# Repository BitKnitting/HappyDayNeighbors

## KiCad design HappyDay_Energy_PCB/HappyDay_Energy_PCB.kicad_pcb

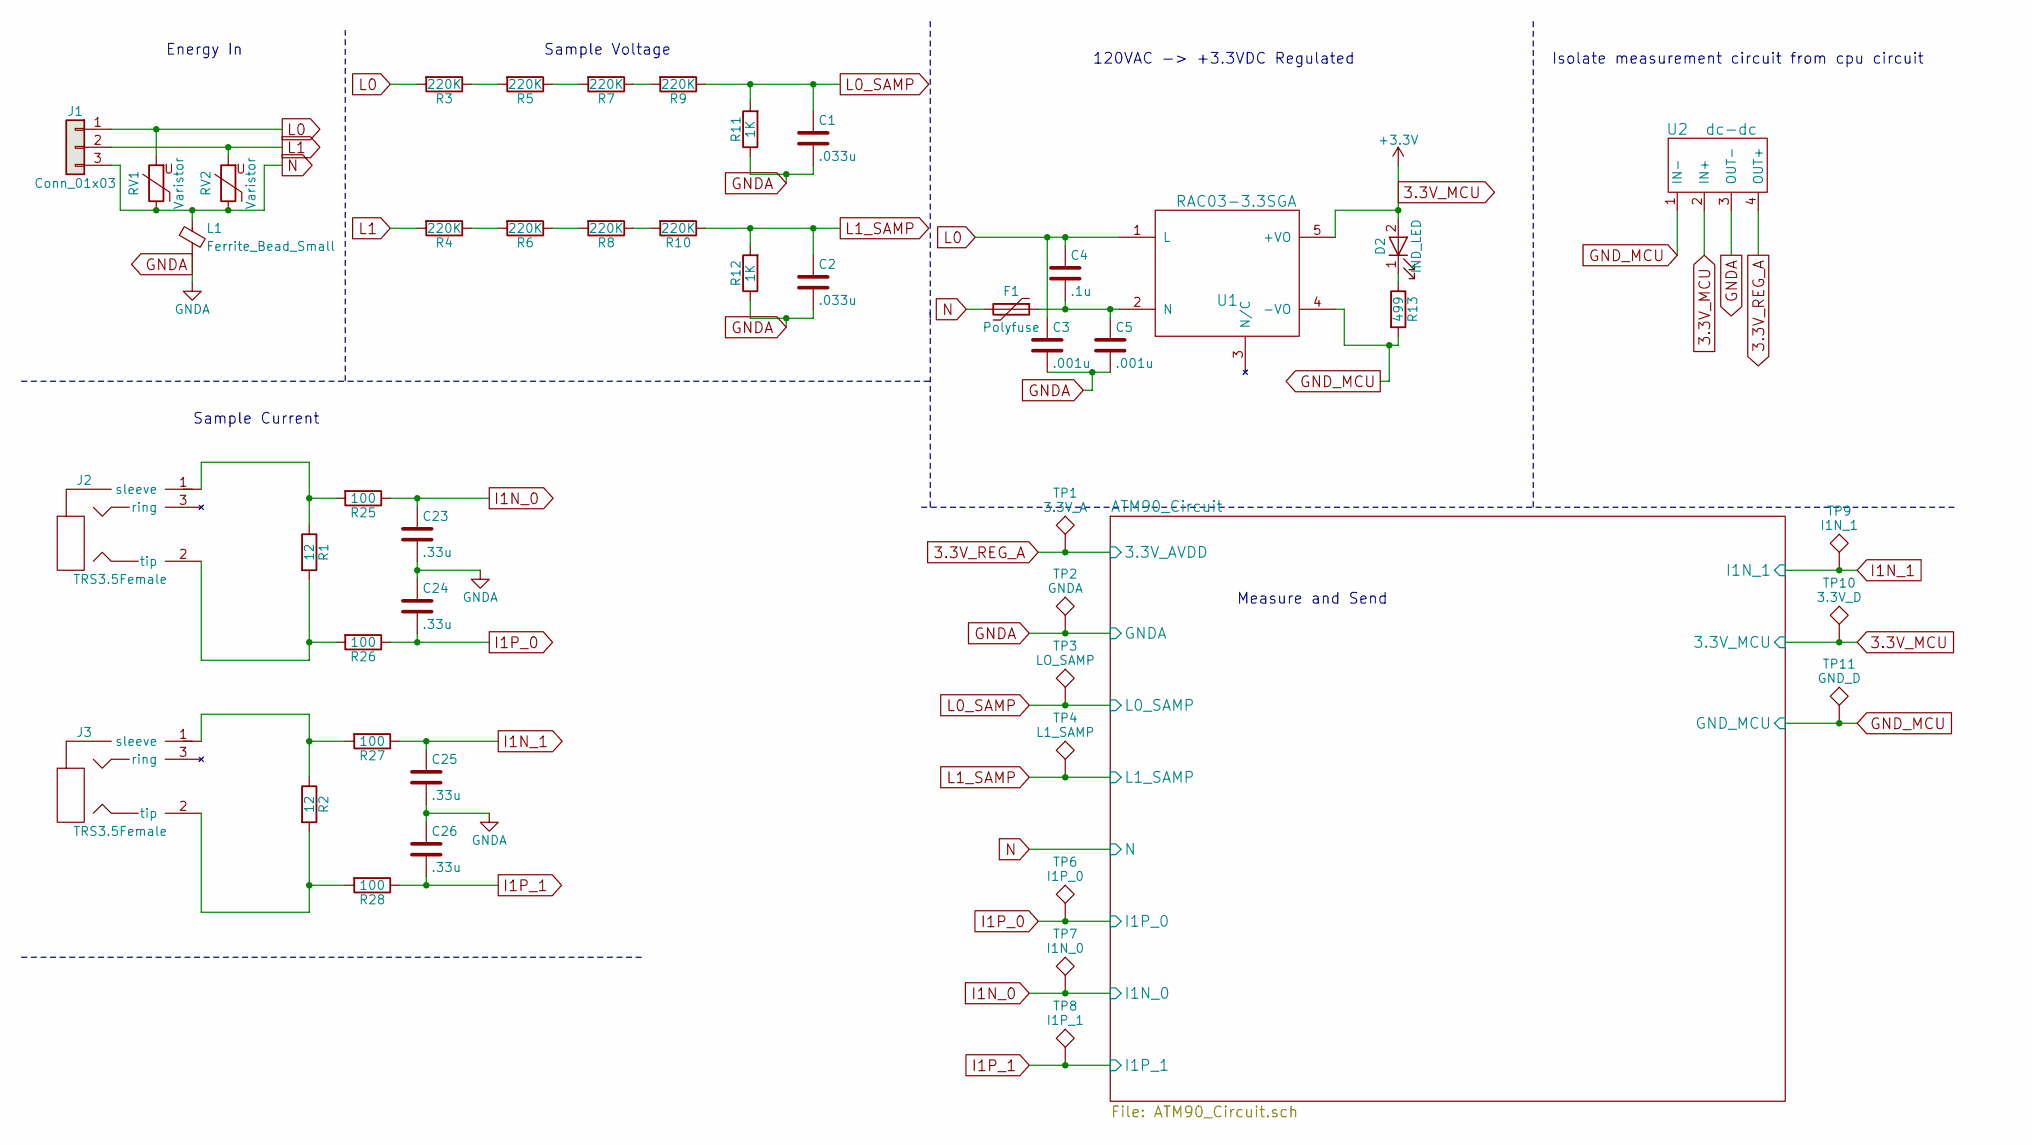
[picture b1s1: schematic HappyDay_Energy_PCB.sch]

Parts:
C1, C2: .033u; C_0805
C3, C5: .001u; C_0805
C4: .1u; C_0805
C23, C24, C25, C26: .33u; C_0805
D2: IND_LED; C_1206_HandSoldering
F1: Polyfuse; POLYFUSE
J1: Conn_01x03; 3PinConnector
J2, J3: TRS3.5Female; Audio-Jack
L1: Ferrite_Bead_Small; C_1206
R1, R2: 12; C_0805
R3, R4, R5, R6, R7, R8, R9, R10: 220K; C_1206
R11, R12: 1K; C_0805
R13: 499; C_0805
R25, R26, R27, R28: 100; C_0805
RV1, RV2: Varistor; MOV
TP1: 3.3V_A; Test_Point_Pad_d2.0mm
TP2: GNDA; Test_Point_Pad_d2.0mm
TP3: LO_SAMP; Test_Point_Pad_d2.0mm
TP4: L1_SAMP; Test_Point_Pad_d2.0mm
TP6: I1P_0; Test_Point_Pad_d2.0mm
TP7: I1N_0; Test_Point_Pad_d2.0mm
TP8: I1P_1; Test_Point_Pad_d2.0mm
TP9: I1N_1; Test_Point_Pad_d2.0mm
TP10: 3.3V_D; Test_Point_Pad_d2.0mm
TP11: GND_D; Test_Point_Pad_d2.0mm
U1: RAC03-3.3SGA; RAC03-GA
U2: dc-dc; DC-DC

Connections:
3.3V_MCU: D2.2 (A), TP10.1, U1.5 (+VO), U2.2 (IN+); also elsewhere on the board
3.3V_REG_A: TP1.1, U2.4 (OUT+); also elsewhere on the board
GNDA: C1.2, C2.2, C3.2, C5.2, C23.2, C24.1, C25.2, C26.1, L1.2, R11.1, R12.1, TP2.1, U2.3 (OUT-); also elsewhere on the board
GND_MCU: R13.2, TP11.1, U1.4 (-VO), U2.1 (IN-); also elsewhere on the board
I1N_0: C23.1, R25.1, TP7.1; also elsewhere on the board
I1N_1: C25.1, R27.1, TP9.1; also elsewhere on the board
I1P_0: C24.2, R26.1, TP6.1; also elsewhere on the board
I1P_1: C26.2, R28.1, TP8.1; also elsewhere on the board
L0: C3.1, C4.1, J1.1, R3.2, RV1.2, U1.1 (L)
L0_SAMP: C1.1, R9.1, R11.2, TP3.1; also elsewhere on the board
L1: J1.2, R4.2, RV2.2
L1_SAMP: C2.1, R10.1, R12.2, TP4.1; also elsewhere on the board
N: F1.2, J1.3, L1.1, RV1.1, RV2.1; also elsewhere on the board
unnamed: C4.2, C5.1, F1.1, U1.2 (N)
unnamed: D2.1 (K), R13.1
unnamed: J2.1 (sleeve), R1.1, R25.2
unnamed: J2.2 (tip), R1.2, R26.2
unnamed: J3.1 (sleeve), R2.1, R27.2
unnamed: J3.2 (tip), R2.2, R28.2
unnamed: R3.1, R5.2
unnamed: R4.1, R6.2
unnamed: R5.1, R7.2
unnamed: R6.1, R8.2
unnamed: R7.1, R9.2
unnamed: R8.1, R10.2

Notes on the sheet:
Energy In
Sample Voltage
Sample Current
120VAC -> +3.3VDC Regulated
Isolate measurement circuit from cpu circuit
Measure and Send

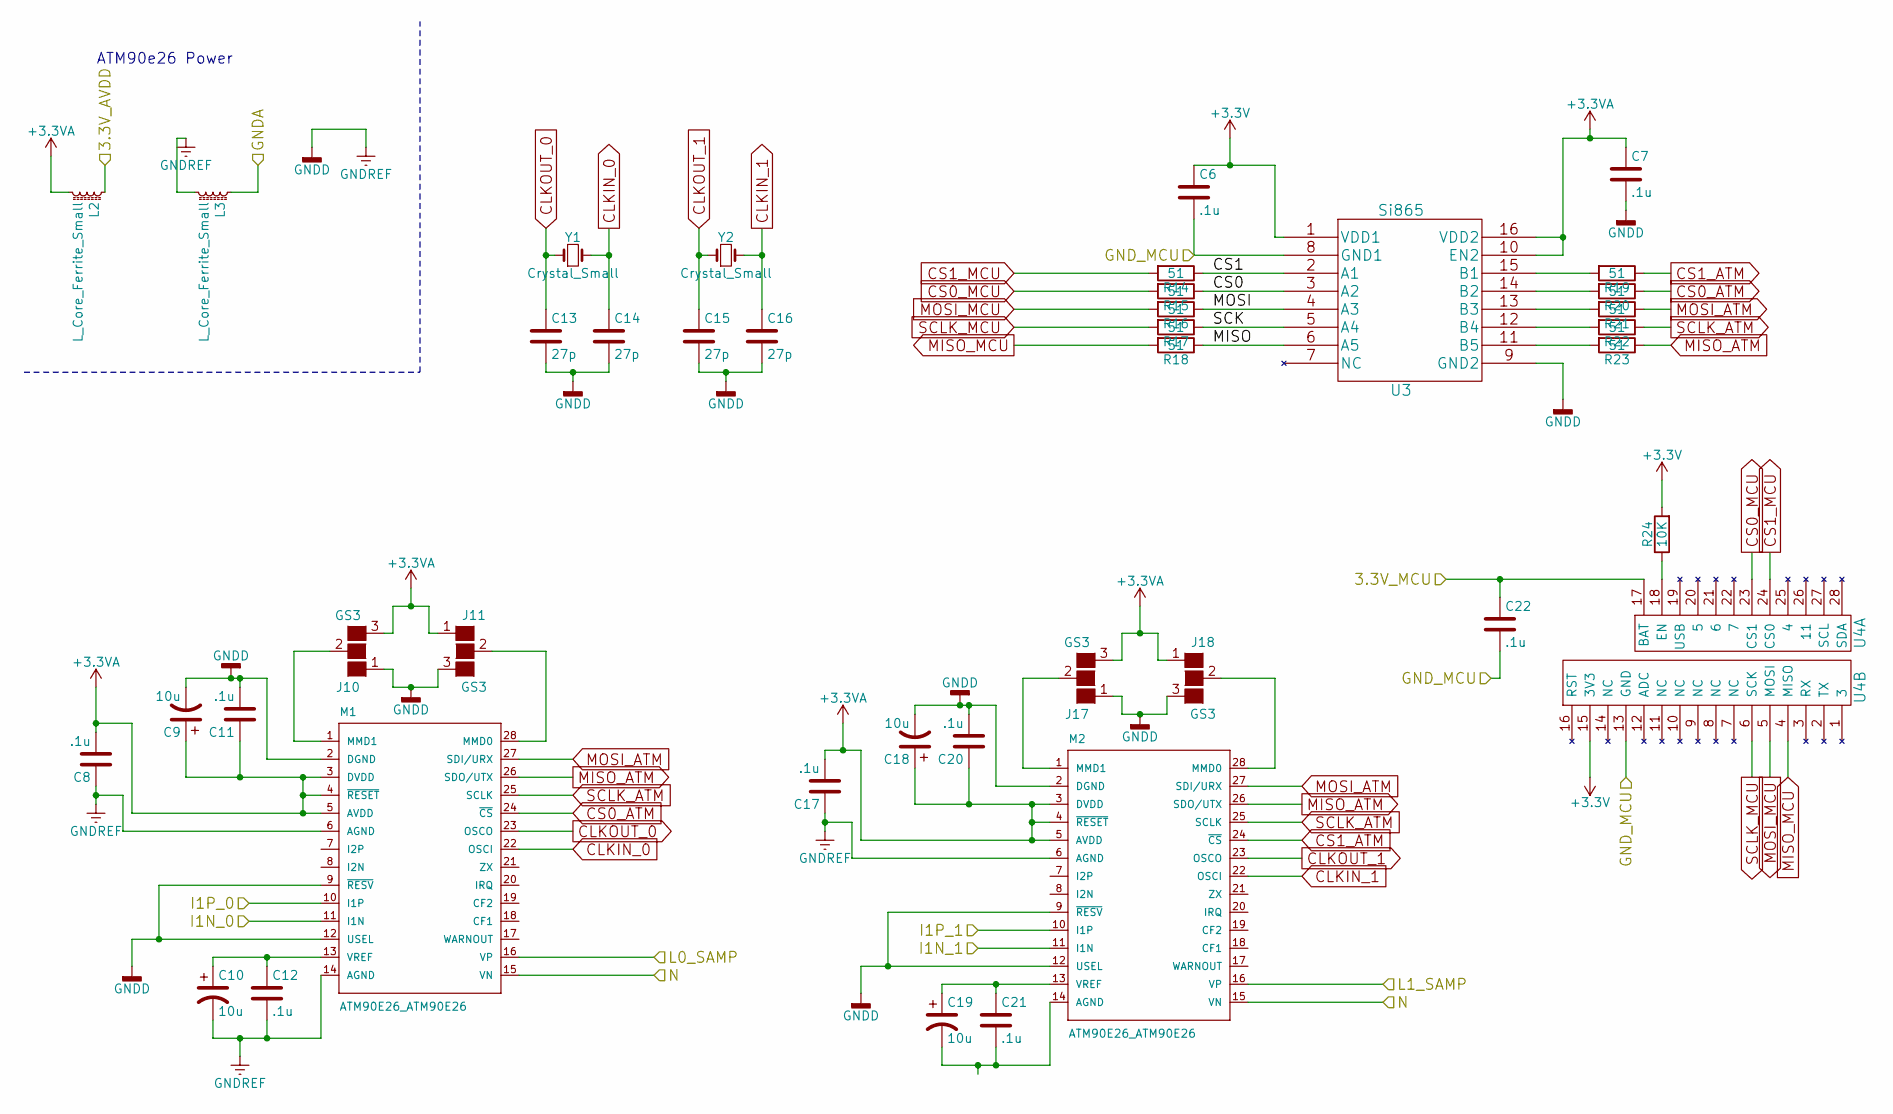
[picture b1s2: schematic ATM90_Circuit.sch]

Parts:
C6, C7, C8, C11, C12, C17, C20, C21, C22: .1u; C_0805
C9, C10, C18, C19: 10u; C_0805
C13, C14, C15, C16: 27p; C_0805
J10, J11, J17, J18: GS3
L2, L3: L_Core_Ferrite_Small; C_0805
M1, M2: ATM90E26_ATM90E26; SSOP-28_5.3x10.2mm_Pitch0.65mm
R14, R15, R16, R17, R18, R19, R20, R21, R22, R23: 51; C_0805
R24: 10K; C_0805
U3: Si865
U4: FeatherHuzzah; ADAFRUIT_FEATHER
Y1, Y2: Crystal_Small; Crystal

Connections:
3.3V_MCU: C6.1, C22.1, R24.2, U3.1 (VDD1), U4.15 (3V3), U4.17 (BAT); also elsewhere on the board
3.3V_REG_A: L2.1; also elsewhere on the board
+3.3VA: C7.1, C8.2, C9.1, C11.1, C17.2, C18.1, C20.1, J10.3 (G3), J11.1 (G1), J17.3 (G3), J18.1 (G1), L2.2, M1.3 (DVDD), M1.4 (~RESET), M1.5 (AVDD), M2.3 (DVDD), M2.4 (~RESET), M2.5 (AVDD), U3.10 (EN2), U3.16 (VDD2)
/ATM90_Circuit/CS0: R15.1, U3.3 (A2)
/ATM90_Circuit/CS1: R14.1, U3.2 (A1)
/ATM90_Circuit/MISO: R18.1, U3.6 (A5)
/ATM90_Circuit/MOSI: R16.1, U3.4 (A3)
/ATM90_Circuit/SCK: R17.1, U3.5 (A4)
CLKIN_0: C14.1, M1.22 (OSCI), Y1.2
CLKIN_1: C16.1, M2.22 (OSCI), Y2.2
CLKOUT_0: C13.1, M1.23 (OSCO), Y1.1
CLKOUT_1: C15.1, M2.23 (OSCO), Y2.1
CS0_ATM: M1.24 (~CS), R20.1
CS0_MCU: R15.2, U4.23 (CS1)
CS1_ATM: M2.24 (~CS), R19.1
CS1_MCU: R14.2, U4.24 (CS0)
GNDA: L3.1; also elsewhere on the board
GNDD: C7.2, C8.1, C9.2, C10.2, C11.2, C12.2, C13.2, C14.2, C15.2, C16.2, C17.1, C18.2, C20.2, J10.1 (G1), J11.3 (G3), J17.1 (G1), J18.3 (G3), L3.2, M1.2 (DGND), M1.6 (AGND), M1.9 (~RESV), M1.12 (USEL), M1.14 (AGND), M2.2 (DGND), M2.6 (AGND), M2.9 (~RESV), M2.12 (USEL), U3.9 (GND2)
GND_MCU: C6.2, C22.2, U3.8 (GND1), U4.13 (GND); also elsewhere on the board
I1N_0: M1.11 (I1N); also elsewhere on the board
I1N_1: M2.11 (I1N); also elsewhere on the board
I1P_0: M1.10 (I1P); also elsewhere on the board
I1P_1: M2.10 (I1P); also elsewhere on the board
L0_SAMP: M1.16 (VP); also elsewhere on the board
L1_SAMP: M2.16 (VP); also elsewhere on the board
MISO_ATM: M1.26 (SDO/UTX), M2.26 (SDO/UTX), R23.1
MISO_MCU: R18.2, U4.4 (MISO)
MOSI_ATM: M1.27 (SDI/URX), M2.27 (SDI/URX), R21.1
MOSI_MCU: R16.2, U4.5 (MOSI)
N: M1.15 (VN), M2.15 (VN); also elsewhere on the board
unnamed: C10.1, C12.1, M1.13 (VREF)
unnamed: C19.1, C21.1, M2.13 (VREF)
unnamed: C19.2, C21.2, M2.14 (AGND)
unnamed: J10.2 (G2), M1.1 (MMD1)
unnamed: J11.2 (G2), M1.28 (MMD0)
unnamed: J17.2 (G2), M2.1 (MMD1)
unnamed: J18.2 (G2), M2.28 (MMD0)
unnamed: R19.2, U3.15 (B1)
unnamed: R20.2, U3.14 (B2)
unnamed: R21.2, U3.13 (B3)
unnamed: R22.2, U3.12 (B4)
unnamed: R23.2, U3.11 (B5)
unnamed: R24.1, U4.18 (EN)
SCLK_ATM: M1.25 (SCLK), M2.25 (SCLK), R22.1
SCLK_MCU: R17.2, U4.6 (SCK)

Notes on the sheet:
ATM90e26 Power

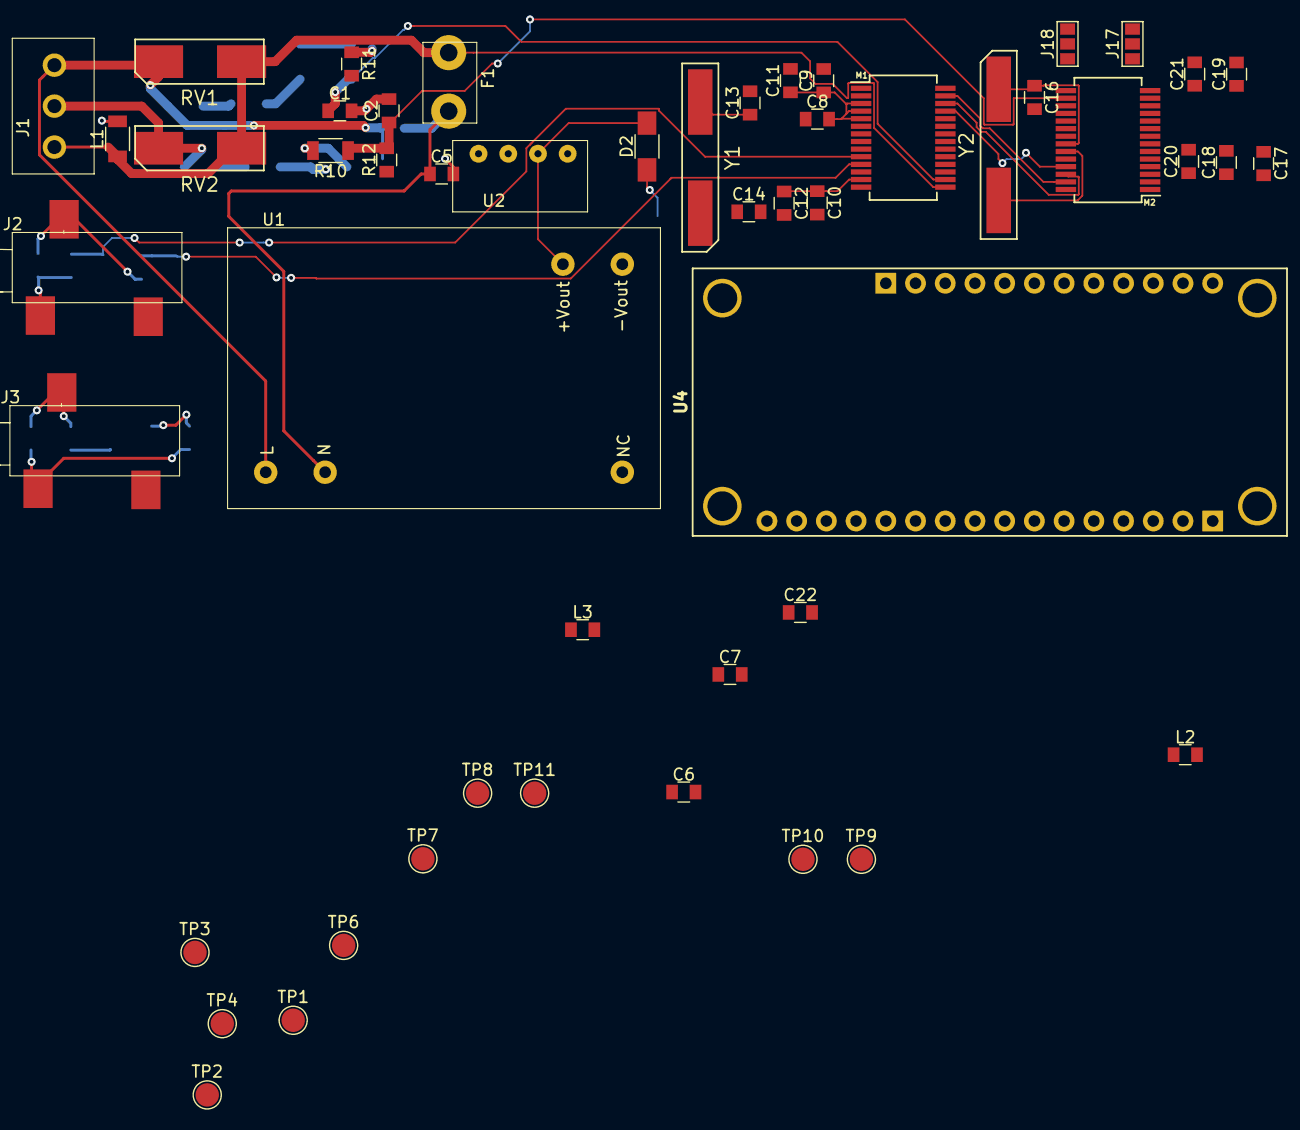
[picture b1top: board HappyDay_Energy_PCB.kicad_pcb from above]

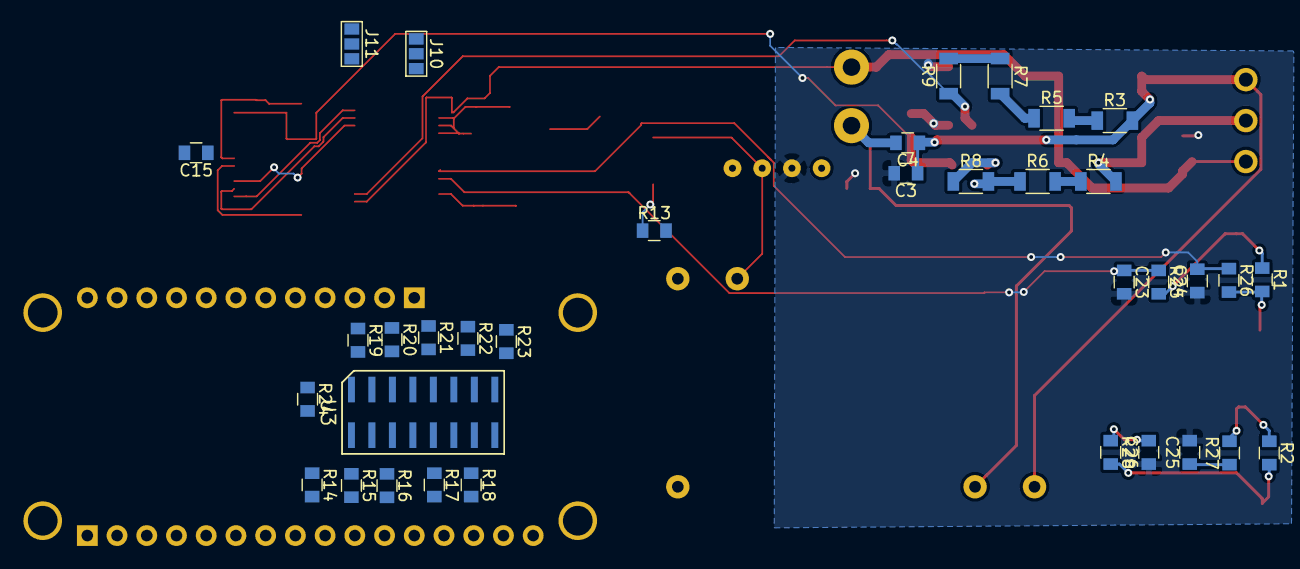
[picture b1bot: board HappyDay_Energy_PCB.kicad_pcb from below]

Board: 2 copper layers, 86 parts (35 on the bottom side), 59 nets.

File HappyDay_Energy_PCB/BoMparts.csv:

Reference,Value,Quantity,Manf Part #
"R11,R12",1K,2,RC0805JR-071KL
"C1,C2",.033u,2,08055C333KAT2A
"RV1,RV2",Varistor,2,B72660M0251K072
L1,Ferrite_Bead_Small,1,HI1206T500R-10
F1,Polyfuse,1,LVR005NK
"R1,R2",12,2,RL1220S-120-F
R13,499,1,RC0805FR-07499RL
D2,IND_LED,1,LTST-C150GKT
"R3,R5,R7,R9,R4,R6,R8,R10",220K,8,CHV1206-JW-224ELF
"C5,C3",.001u,2,202R18W102KV4E
C4,.1u,1,GRM32DR72H104KW10L
U2,dc-dc,1,CRE1S0505S3C
"J2,J3",TRS3.5Female,2,SJ-3523-SMT-TR
J1,Conn_01x03,1,OSTTE030161
"R25,R26,R27,R28",100,4,RC0805FR-07100RL
"C23,C24,C25,C26",.33u,4,CL21B334KAFNNNG
U1,RAC03-3.3SGA,1,RAC04-3.3SGB
"C11,C12,C8,C20,C21,C17,C6,C7,C22",.1u,9,CL21F104ZBCNNNC
"C9,C10,C18,C19",10u,4,CL21A106KQCLRNC
"Y1,Y2",Crystal_Small,2,ABLS2-3.579545MHZ-D4Y-T
"C13,C14,C15,C16",27p,4,500R15N270KV4T
"L2,L3",L_Core_Ferrite_Small,2,MH2029-601Y
"R14,R15,R16,R17,R19,R20,R21,R22,R23,R18",51,10,RMCF0805JT51R0
R24,10K,1,C0805JR-0710KL
"M2,M1",ATM90E26_ATM90E26,2,ATM90E26-YU-B
U3,Si865,1,SI8652AB-B-IS1

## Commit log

2017-11-20 added PCB schematic sacrificial draft
2017-11-24 sacrificial draft of power section / HappyDay Energy Monitor Schematic
2017-11-24 evolved schematic
2017-12-04 evolved layout
2017-12-05 Kicad PCB sent to OSH Park
2017-12-07 files sent to OSH Park for sacrificial draft build
2017-12-17 added a css file
2017-12-17 added label-picker snippet html
2017-12-27 updates, particularly to layout - but not finished
